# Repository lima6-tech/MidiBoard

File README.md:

# MidiBoard
A custom midi board PCB. Features hexagon shaped touch capacity keys, switches with LEDs and rotary encoders + potentiometer sliders. 

## Components

| Component | Quantity |
| --- | --- |
| LED SK6812MINI-E | 3 |
| Capacity Keys (Capacitive keys) | 1 |
| Potentiometer Bourn Single_Slide | 2 |
| Cherry MX Switches | 3 |
| RotaryEncoder Alps EC11E-Switch Vertical H20mm | 1 |
| Waveshare ESP32-S3-Zero | 1 |

## Firmware
Done with Circuit python. The capacity keys play notes (A-G). The different midi board components have been set to do different note adjustment functions (controlling midi cc values). I might later change the middle (2nd) key to change key layers. 

| Component | Function |
| --- | --- |
| Left switch | Raises the notes played by an octave |
| Center switch | pause / play |
| Right switch | Lowers the notes played by an octave |
| Rotary Encoder | controls volume |
| Slider 1 | note modulation |
| Slider  | note resonance

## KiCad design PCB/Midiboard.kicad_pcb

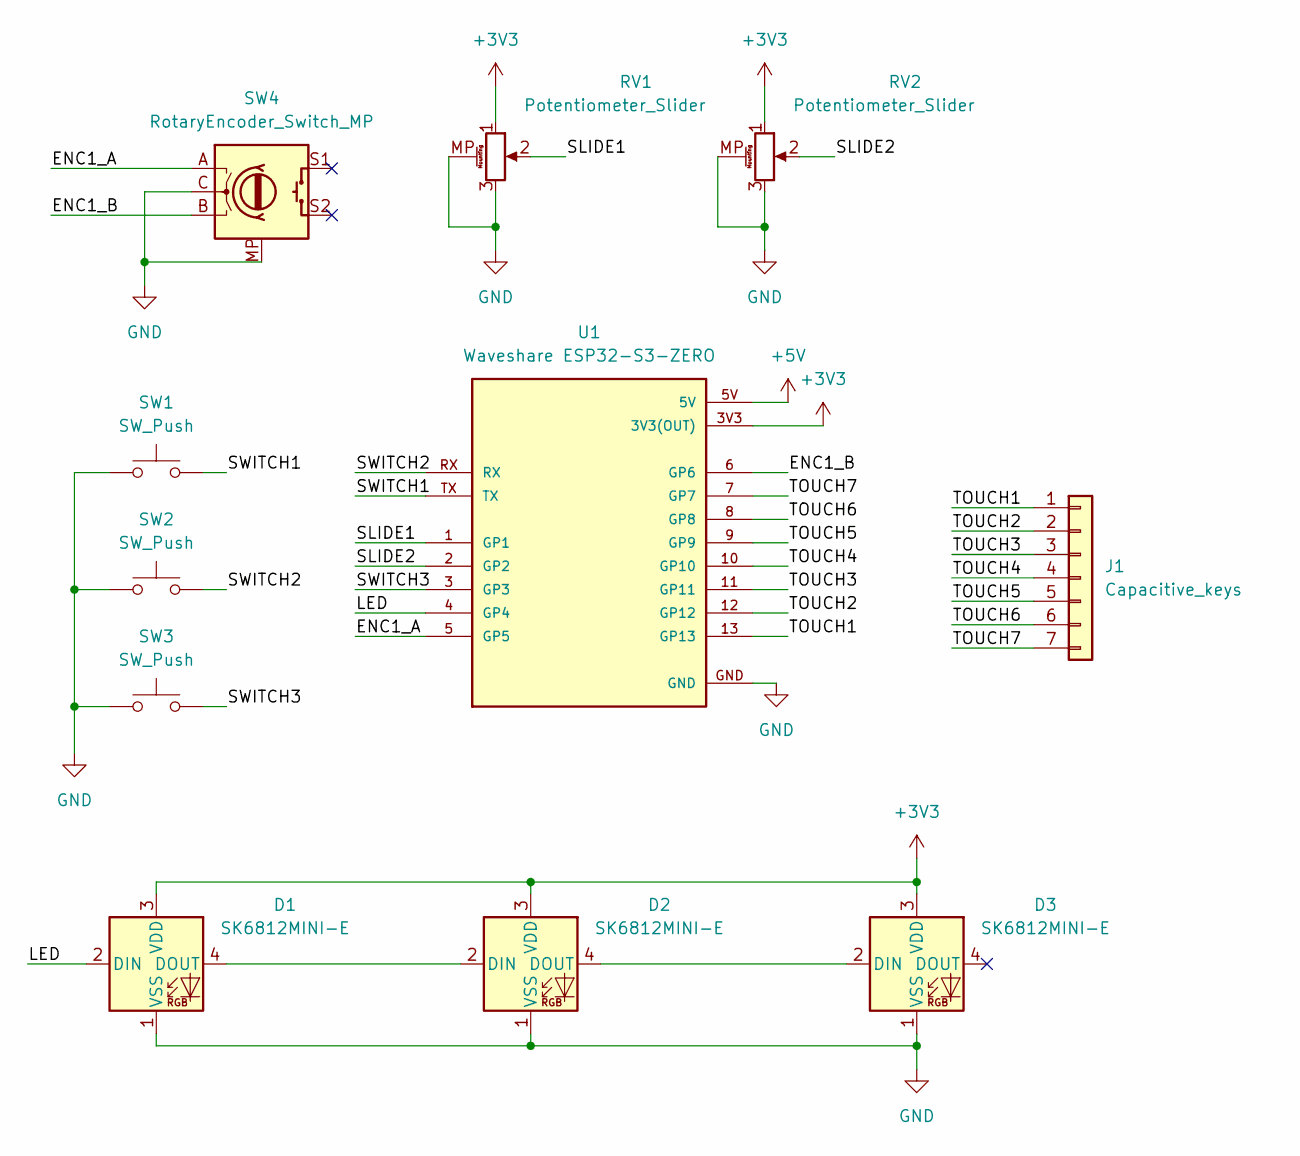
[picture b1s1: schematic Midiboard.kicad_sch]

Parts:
D1, D2, D3: SK6812MINI-E; LED_SK6812MINI-E_3.2x2.8mm_P1.5mm_ReverseMount; LCSC Part # C5149201
J1: Capacitive_keys; CapacityKeys; LCSC Part # C2932700
RV1, RV2: Potentiometer_Slider; Potentiometer_Bourns_PTA2043_Single_Slide; LCSC Part # C5272874
SW1, SW2, SW3: SW_Push; SW_Cherry_MX_1.00u_PCB
SW4: RotaryEncoder_Switch_MP; RotaryEncoder_Alps_EC11E-Switch_Vertical_H20mm; LCSC Part # C470754
U1: Waveshare ESP32-S3-ZERO; Waveshare ESP32-S3-Zero; PARTREV NA; LCSC C9900190773

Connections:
+3V3: D1.3 (VDD), D2.3 (VDD), D3.3 (VDD), RV1.1, RV2.1, U1.3V3 (3V3(OUT))
+5V: U1.5V
/ENC1_A: SW4.A, U1.5 (GP5)
/ENC1_B: SW4.B, U1.6 (GP6)
/LED: D1.2 (DIN), U1.4 (GP4)
/SLIDE1: RV1.2, U1.1 (GP1)
/SLIDE2: RV2.2, U1.2 (GP2)
/SWITCH1: SW1.2, U1.TX
/SWITCH2: SW2.2, U1.RX
/SWITCH3: SW3.2, U1.3 (GP3)
/TOUCH1: J1.1, U1.13 (GP13)
/TOUCH2: J1.2, U1.12 (GP12)
/TOUCH3: J1.3, U1.11 (GP11)
/TOUCH4: J1.4, U1.10 (GP10)
/TOUCH5: J1.5, U1.9 (GP9)
/TOUCH6: J1.6, U1.8 (GP8)
/TOUCH7: J1.7, U1.7 (GP7)
GND: D1.1 (VSS), D2.1 (VSS), D3.1 (VSS), RV1.3, RV1.MP (MountPin), RV2.3, RV2.MP (MountPin), SW1.1, SW2.1, SW3.1, SW4.C, SW4.MP, U1.GND
unnamed: D1.4 (DOUT), D2.2 (DIN)
unnamed: D2.4 (DOUT), D3.2 (DIN)

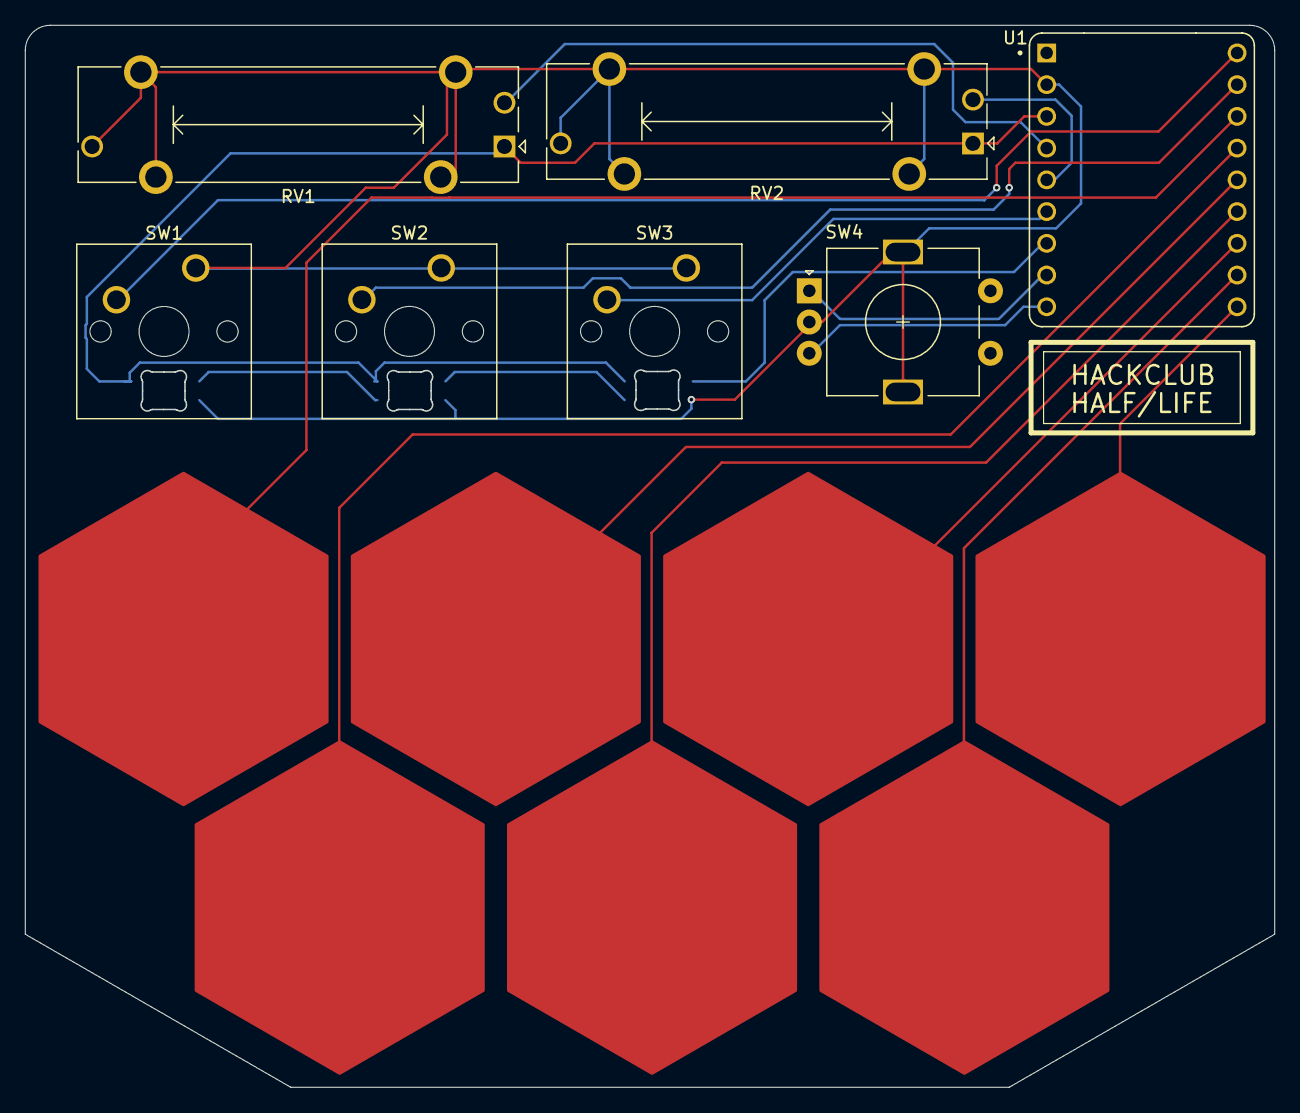
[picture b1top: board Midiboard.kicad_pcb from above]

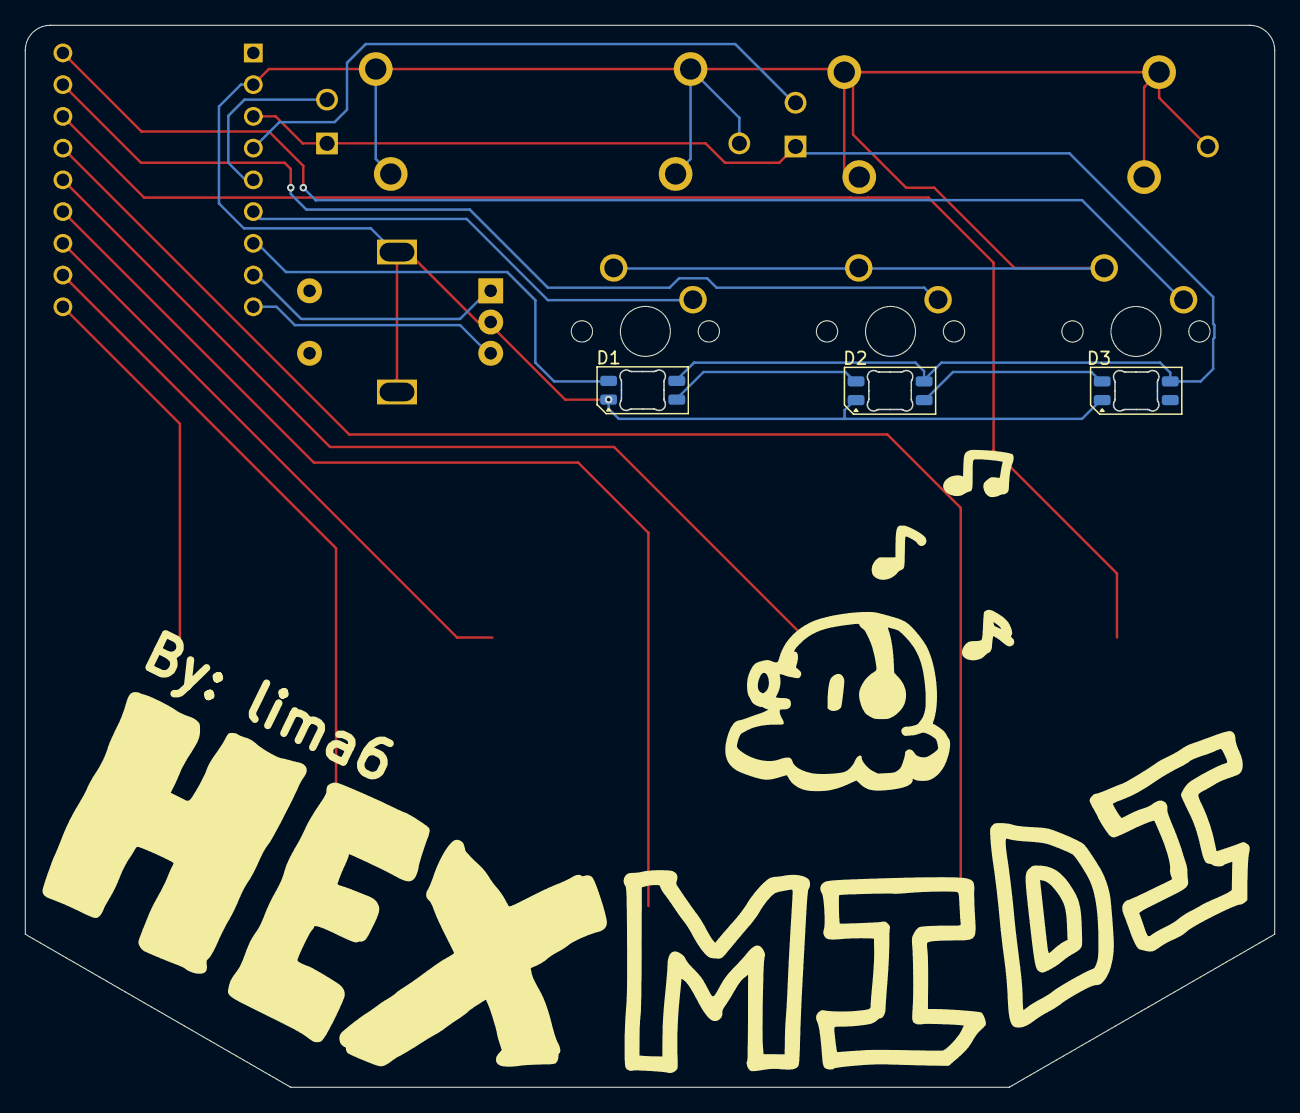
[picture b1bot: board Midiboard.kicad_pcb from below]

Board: 2 copper layers, 100.0 x 85.0 mm, 11 parts (3 on the bottom side), 19 nets.

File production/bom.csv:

Designator,Footprint,Quantity,Value,LCSC Part #
"D1, D2, D3",LED_SK6812MINI-E_3.2x2.8mm_P1.5mm_ReverseMount,3,SK6812MINI-E,C5149201
J1,CapacityKeys,1,Capacitive_keys,C2932700
"RV1, RV2",Potentiometer_Bourns_PTA2043_Single_Slide,2,Potentiometer_Slider,C5272874
"SW1, SW2, SW3",SW_Cherry_MX_1.00u_PCB,3,SW_Push,
SW4,RotaryEncoder_Alps_EC11E-Switch_Vertical_H20mm,1,RotaryEncoder_Switch_MP,C470754
U1,Waveshare ESP32-S3-Zero,1,Waveshare ESP32-S3-ZERO,C9900190773
